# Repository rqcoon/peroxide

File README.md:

# peroxide
ATMega32u4-based keyboard

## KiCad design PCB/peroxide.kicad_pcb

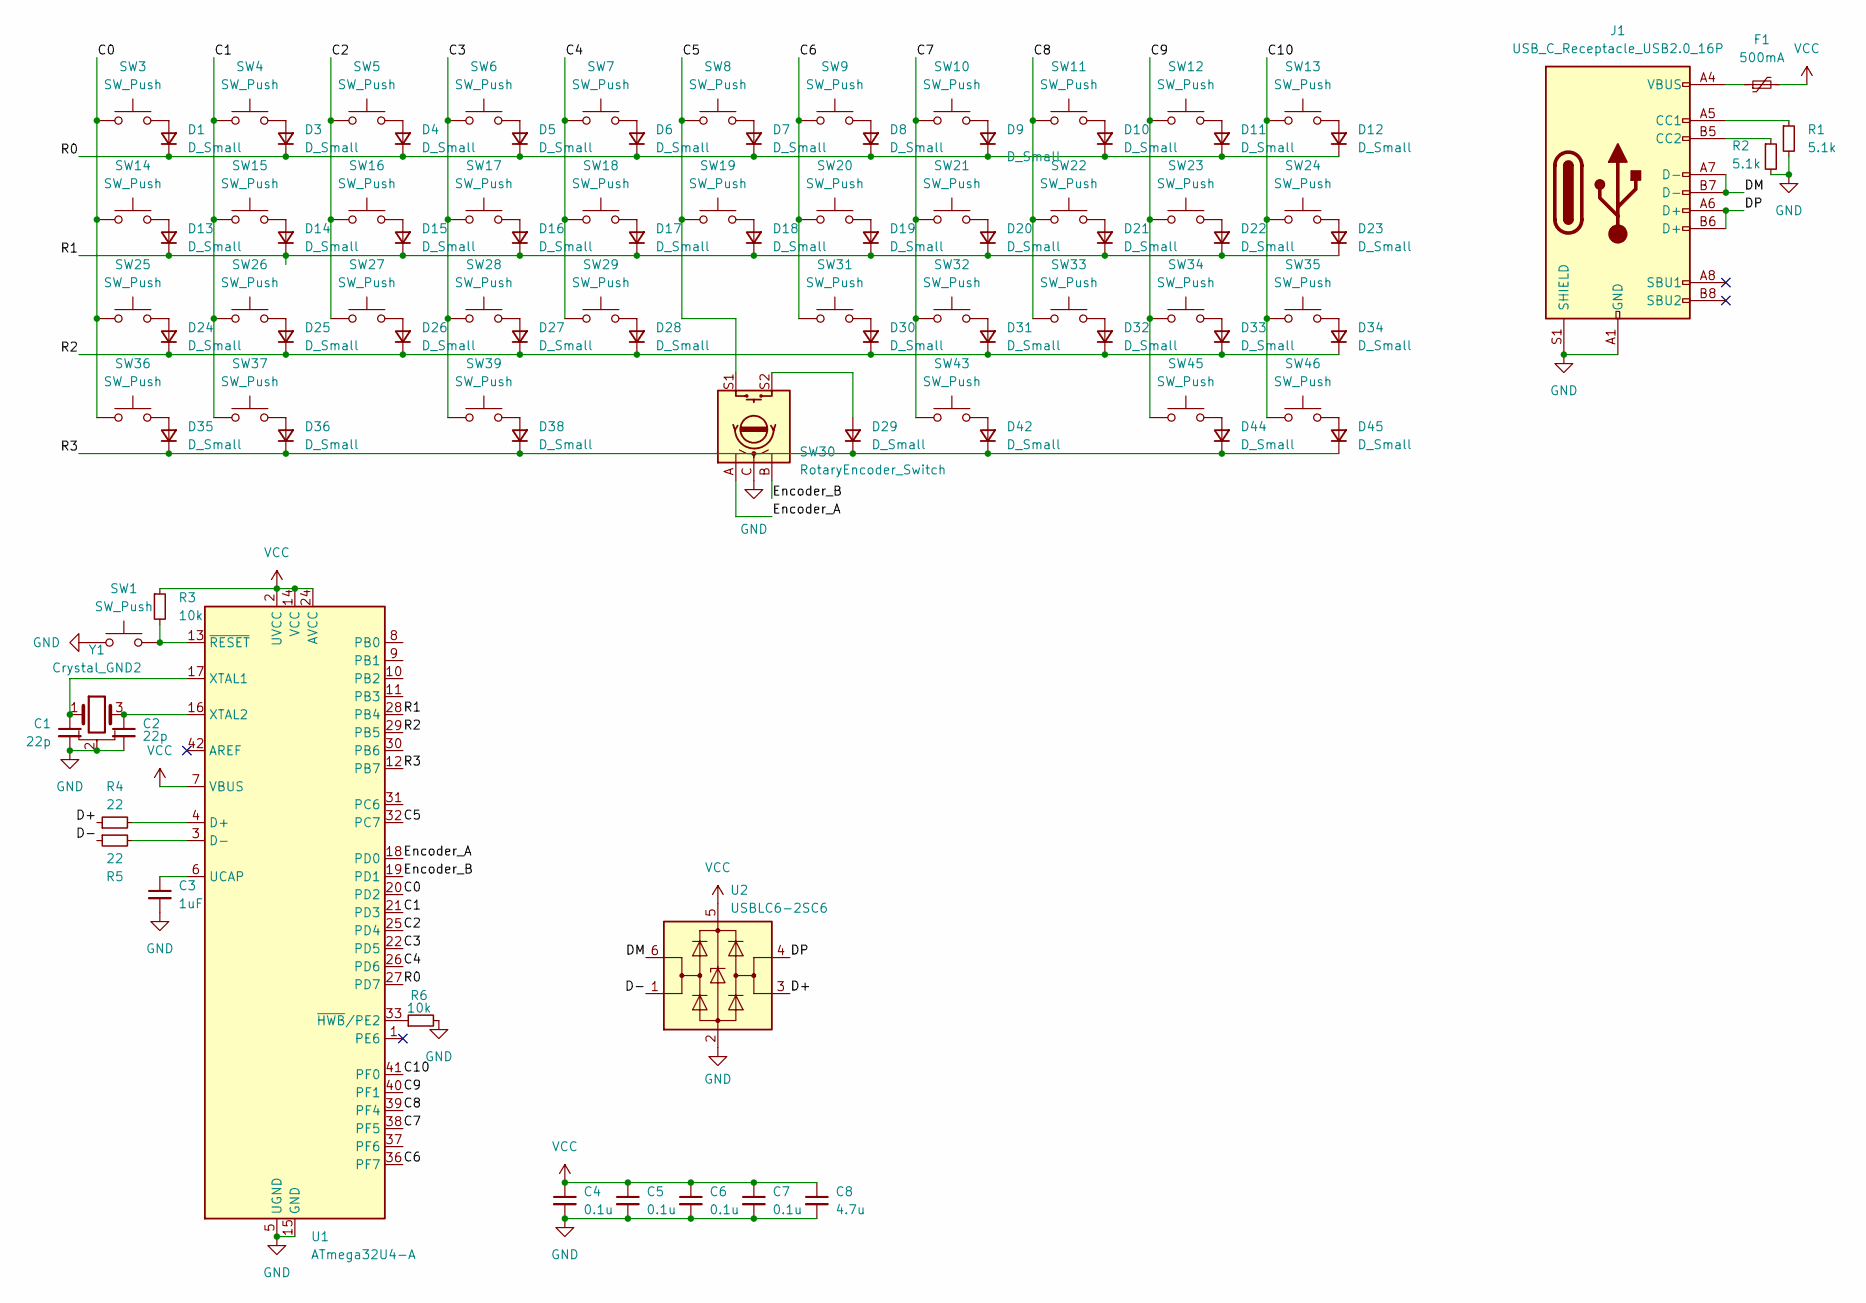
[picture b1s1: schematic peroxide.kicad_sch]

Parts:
C1, C2: 22p; C_0805_2012Metric_Pad1.18x1.45mm_HandSolder
C3: 1uF; C_0805_2012Metric_Pad1.18x1.45mm_HandSolder
C4, C5, C6, C7: 0.1u; C_0805_2012Metric_Pad1.18x1.45mm_HandSolder
C8: 4.7u; C_0805_2012Metric_Pad1.18x1.45mm_HandSolder
D1, D3, D4, D5, D6, D7, D8, D9, D10, D11, D12, D13, D14, D15, D16, D17, D18, D19, D20, D21, D22, D23, D24, D25, D26, D27, D28, D29, D30, D31, D32, D33, D34, D35, D36, D38, D42, D44, D45: D_Small; D_0805_2012Metric_Pad1.15x1.40mm_HandSolder
F1: 500mA; Fuse_0805_2012Metric_Pad1.15x1.40mm_HandSolder
J1: USB_C_Receptacle_USB2.0_16P; USB_C_Receptacle_HRO_TYPE-C-31-M-12
R1, R2: 5.1k; R_0805_2012Metric_Pad1.20x1.40mm_HandSolder
R3, R6: 10k; R_0805_2012Metric_Pad1.20x1.40mm_HandSolder
R4, R5: 22; R_0805_2012Metric_Pad1.20x1.40mm_HandSolder
SW1: SW_Push; SW_SPST_SKQG_WithStem
SW3, SW4, SW5, SW6, SW7, SW8, SW9, SW10, SW11, SW12, SW13, SW14, SW15, SW16, SW17, SW18, SW19, SW20, SW21, SW22, SW23, SW24, SW26, SW27, SW28, SW29, SW31, SW32, SW33, SW34: SW_Push; SW_Cherry_MX_1.00u_PCB
SW25, SW35: SW_Push; SW_Cherry_MX_1.50u_PCB
SW30: RotaryEncoder_Switch; RotaryEncoder_Alps_EC11E-Switch_Vertical_H20mm
SW36, SW37, SW45, SW46: SW_Push; SW_Cherry_MX_1.25u_PCB
SW39, SW43: SW_Push; SW_Cherry_MX_1.75u_PCB
U1: ATmega32U4-A; TQFP-44_10x10mm_P0.8mm
U2: USBLC6-2SC6; SOT-23-6
Y1: Crystal_GND2; Crystal_SMD_3225-4Pin_3.2x2.5mm_HandSoldering

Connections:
/C0: SW3.1, SW14.1, SW25.1, SW36.1, U1.20 (PD2)
/C1: SW4.1, SW15.1, SW26.1, SW37.1, U1.21 (PD3)
/C2: SW5.1, SW16.1, SW27.1, U1.25 (PD4)
/C3: SW6.1, SW17.1, SW28.1, SW39.1, U1.22 (PD5)
/C4: SW7.1, SW18.1, SW29.1, U1.26 (PD6)
/C5: SW8.1, SW19.1, SW30.S1, U1.32 (PC7)
/C6: SW9.1, SW20.1, SW31.1, U1.36 (PF7)
/C7: SW10.1, SW21.1, SW32.1, SW43.1, U1.38 (PF5)
/C8: SW11.1, SW22.1, SW33.1, U1.39 (PF4)
/C9: SW12.1, SW23.1, SW34.1, SW45.1, U1.40 (PF1)
/C10: SW13.1, SW24.1, SW35.1, SW46.1, U1.41 (PF0)
/D+: R4.1, U2.3 (I/O2)
/D-: R5.1, U2.1 (I/O1)
/DM: J1.A7 (D-), J1.B7 (D-), U2.6 (I/O1)
/DP: J1.A6 (D+), J1.B6 (D+), U2.4 (I/O2)
/Encoder_A: SW30.A, U1.18 (PD0)
/Encoder_B: SW30.B, U1.19 (PD1)
/R0: D1.1 (K), D3.1 (K), D4.1 (K), D5.1 (K), D6.1 (K), D7.1 (K), D8.1 (K), D9.1 (K), D10.1 (K), D11.1 (K), D12.1 (K), U1.27 (PD7)
/R1: D13.1 (K), D14.1 (K), D15.1 (K), D16.1 (K), D17.1 (K), D18.1 (K), D19.1 (K), D20.1 (K), D21.1 (K), D22.1 (K), D23.1 (K), U1.28 (PB4)
/R2: D24.1 (K), D25.1 (K), D26.1 (K), D27.1 (K), D28.1 (K), D30.1 (K), D31.1 (K), D32.1 (K), D33.1 (K), D34.1 (K), U1.29 (PB5)
/R3: D29.1 (K), D35.1 (K), D36.1 (K), D38.1 (K), D42.1 (K), D44.1 (K), D45.1 (K), U1.12 (PB7)
GND: C1.2, C2.2, C3.2, C4.2, C5.2, C6.2, C7.2, C8.2, J1.A1 (GND), J1.A12 (GND), J1.B1 (GND), J1.B12 (GND), J1.S1 (SHIELD), R1.2, R2.2, R6.2, SW1.1, SW30.C, U1.5 (UGND), U1.15 (GND), U1.23 (GND), U1.35 (GND), U1.43 (GND), U2.2 (GND), Y1.2
unnamed: D1.2 (A), SW3.2
unnamed: D3.2 (A), SW4.2
unnamed: D4.2 (A), SW5.2
unnamed: D5.2 (A), SW6.2
unnamed: D6.2 (A), SW7.2
unnamed: D7.2 (A), SW8.2
unnamed: D8.2 (A), SW9.2
unnamed: D9.2 (A), SW10.2
unnamed: D10.2 (A), SW11.2
unnamed: D11.2 (A), SW12.2
unnamed: D12.2 (A), SW13.2
unnamed: D13.2 (A), SW14.2
unnamed: D14.2 (A), SW15.2
unnamed: D15.2 (A), SW16.2
unnamed: D16.2 (A), SW17.2
unnamed: D17.2 (A), SW18.2
unnamed: D18.2 (A), SW19.2
unnamed: D19.2 (A), SW20.2
unnamed: D20.2 (A), SW21.2
unnamed: D21.2 (A), SW22.2
unnamed: D22.2 (A), SW23.2
unnamed: D23.2 (A), SW24.2
unnamed: D24.2 (A), SW25.2
unnamed: D25.2 (A), SW26.2
unnamed: D26.2 (A), SW27.2
unnamed: D27.2 (A), SW28.2
unnamed: D28.2 (A), SW29.2
unnamed: D29.2 (A), SW30.S2
unnamed: D30.2 (A), SW31.2
unnamed: D31.2 (A), SW32.2
unnamed: D32.2 (A), SW33.2
unnamed: D33.2 (A), SW34.2
unnamed: D34.2 (A), SW35.2
unnamed: D35.2 (A), SW36.2
unnamed: D36.2 (A), SW37.2
unnamed: D38.2 (A), SW39.2
unnamed: D42.2 (A), SW43.2
unnamed: D44.2 (A), SW45.2
unnamed: D45.2 (A), SW46.2
unnamed: F1.1, J1.A4 (VBUS), J1.A9 (VBUS), J1.B4 (VBUS), J1.B9 (VBUS)
unnamed: J1.A5 (CC1), R1.1
unnamed: J1.B5 (CC2), R2.1
unnamed: R4.2, U1.4 (D+)
unnamed: R5.2, U1.3 (D-)
unnamed: C3.1, U1.6 (UCAP)
unnamed: C1.1, U1.17 (XTAL1), Y1.1
unnamed: C2.1, U1.16 (XTAL2), Y1.3
unnamed: R6.1, U1.33 (~HWB/PE2)
unnamed: R3.2, SW1.2, U1.13 (~RESET)
VCC: C4.1, C5.1, C6.1, C7.1, C8.1, F1.2, R3.1, U1.2 (UVCC), U1.7 (VBUS), U1.14 (VCC), U1.24 (AVCC), U1.34 (VCC), U1.44 (AVCC), U2.5 (VBUS)

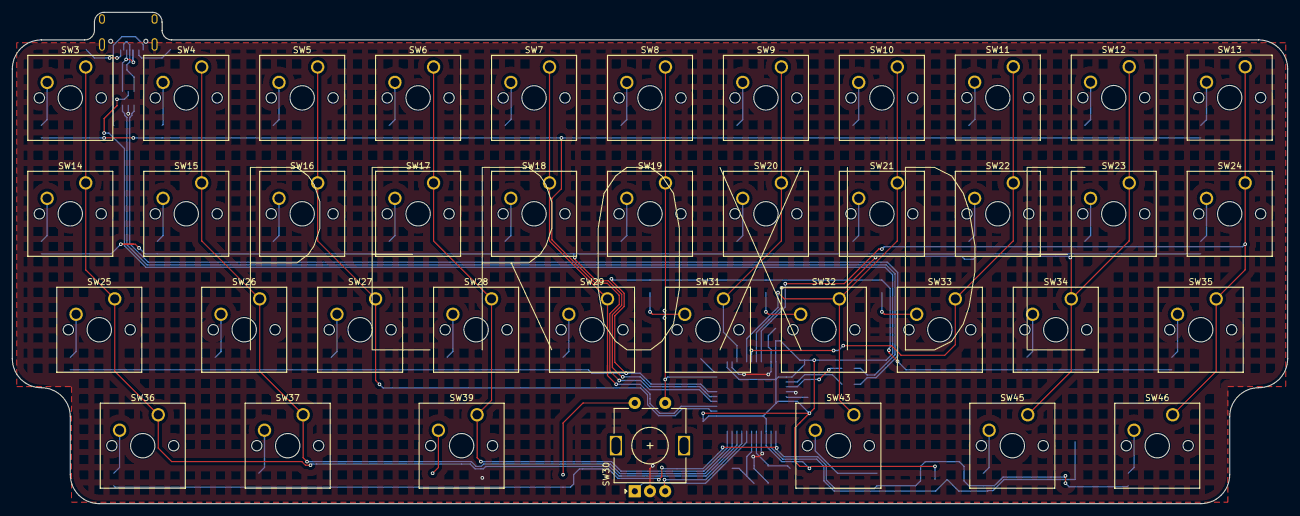
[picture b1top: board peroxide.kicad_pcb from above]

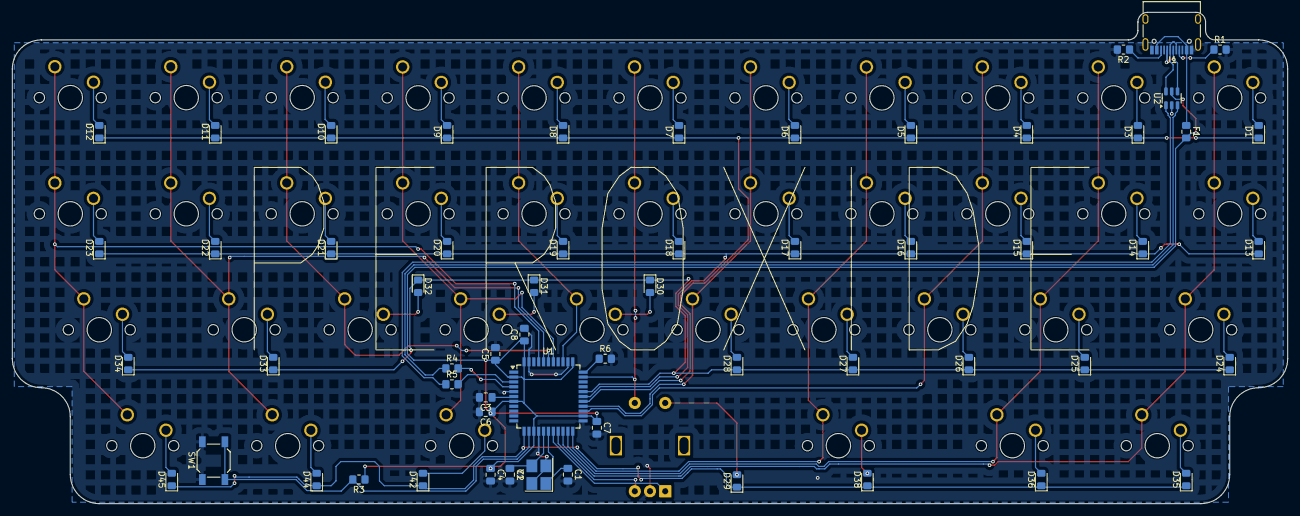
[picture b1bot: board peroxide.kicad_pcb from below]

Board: 2 copper layers, 209.5 x 80.7 mm, 98 parts (59 on the bottom side), 72 nets.

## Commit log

2024-09-09 PCB Revision 1.1
    First upload, ESD protection added
2024-09-09 add .gitignore
